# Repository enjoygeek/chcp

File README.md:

chcp
====

PoE powered, IPv6 Central Heating Control Panel

Photo of circuit board:

More photos in this gallery on Flickr:
https://www.flickr.com/photos/njh/sets/72157648035750106/

ATMEGA328 Pin Mapping
----------------------

| Pin | Port | Arduino | Function    |
|-----|------|---------|-------------|
| 1   | RST# |         |             |
| 2   | D0   | D0      | Serial RX   |
| 3   | D1   | D1      | Serial TX   |
| 4   | D2   | D2      |             |
| 5   | D3   | D3      | LCD LIGHT   |
| 6   | D4   | D4      |             |
| 7   | VCC  |         |             |
| 8   | GND  |         |             |
| 9   | CLK  |         |             |
| 10  | CLK  |         |             |
| 11  | D5   | D5      | Push Button |
| 12  | D6   | D6      | Red LED     |
| 13  | D7   | D7      | Ethernet SS |
| 14  | B0   | D8      | LCD RESET   |
| 15  | B1   | D9      | LCD SS      |
| 16  | B2   | D10     | LCD DC      |
| 17  | B3   | D11     | SPI MOSI    |
| 18  | B4   | D12     | SPI MISO    |
| 19  | B5   | D13     | SPI SCLK    |
| 20  | VCC  |         |             |
| 21  | Aref |         |             |
| 22  | GND  |         |             |
| 23  | C0   | A0      |             |
| 24  | C1   | A1      |             |
| 25  | C2   | A2      |             |
| 26  | C3   | A3      |             |
| 27  | C4   | A4      | I2C SDA     |
| 28  | C5   | A5      | I2C SCL     |

PoE Pin Mapping
---------------

| RJ45 | IN28J60 | PEM1300 |
|------|---------|---------|
| 1+2  | POE+1   | VA1     |
| 3+6  | POE-1   | VA2     |
| 4+5  | POE-2   | VB1     |
| 7+8  | POE+2   | VB2     |

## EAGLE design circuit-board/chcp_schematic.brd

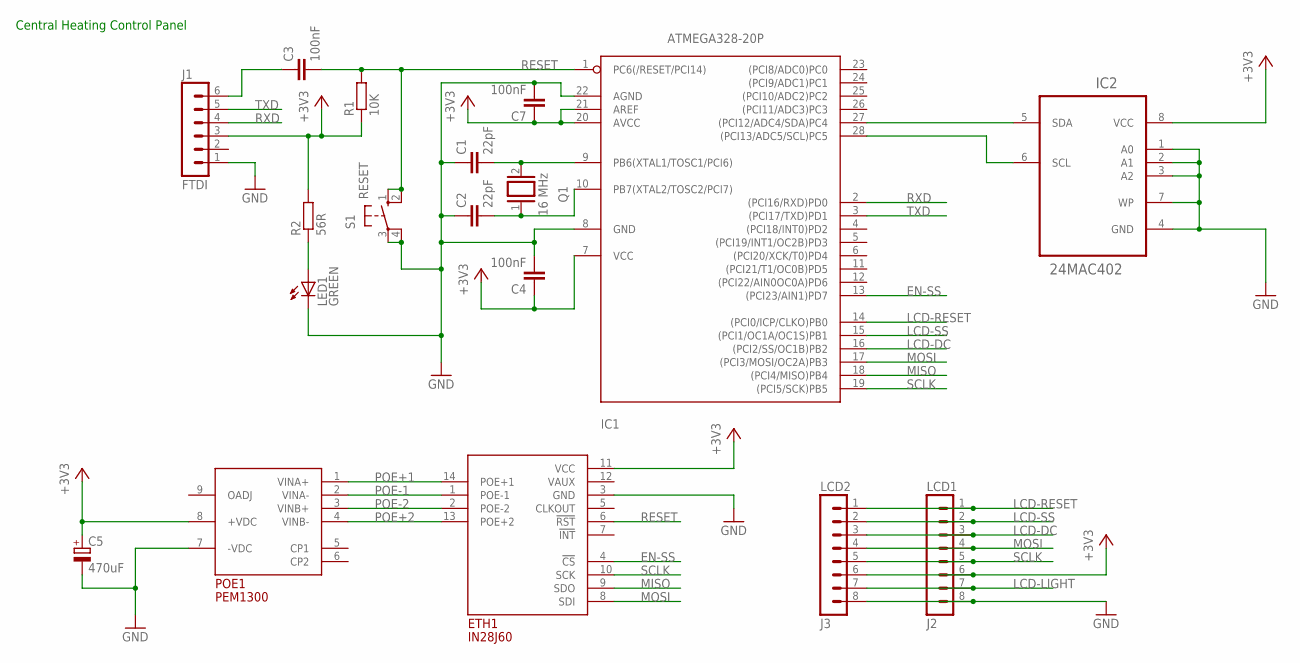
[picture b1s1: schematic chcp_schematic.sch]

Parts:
C1, C2: 22pF; C025-024X044
C3, C4, C7: 100nF; C025-024X044
C5: 470uF; E2,5-5
ETH1: IN28J60; DIL
IC1: ATMEGA328-20P; DIL28-3
IC2: 24MAC402; PDIP
J1: FTDI; MA06-1
J2: LCD1; MA08-1
J3: LCD2; MA08-1
LED1: GREEN; LED3MM
POE1: PEM1300; SIL
Q1: 16 MHz; QS
R1: 10K; 0204/7
R2: 56R; 0204/7
S1: RESET; B3F-10XX

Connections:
+3V3: C4.1, C5.+, C7.1, ETH1.11 (VCC), IC1.7 (VCC), IC1.20 (AVCC), IC1.21 (AREF), IC2.8 (VCC), J1.3, J2.6, J3.6, POE1.8 (+VDC), R1.1, R2.2
EN-SS: ETH1.4 (!CS!), IC1.13 ((PCI23/AIN1)PD7)
GND: C1.1, C2.1, C4.2, C5.-, C7.2, ETH1.3 (GND), IC1.8 (GND), IC1.22 (AGND), IC2.1 (A0), IC2.2 (A1), IC2.3 (A2), IC2.4 (GND), IC2.7 (WP), J1.1, J2.8, J3.8, LED1.K (C), POE1.7 (-VDC), S1.3, S1.4 (P1)
LCD-DC: IC1.16 ((PCI2/SS/OC1B)PB2), J2.3, J3.3
LCD-LIGHT: J2.7, J3.7
LCD-RESET: IC1.14 ((PCI0/ICP/CLKO)PB0), J2.1, J3.1
LCD-SS: IC1.15 ((PCI1/OC1A/OC1S)PB1), J2.2, J3.2
MISO: ETH1.9 (SDO), IC1.18 ((PCI4/MISO)PB4)
MOSI: ETH1.8 (SDI), IC1.17 ((PCI3/MOSI/OC2A)PB3), J2.4, J3.4
unnamed: C2.2, IC1.10 (PB7(XTAL2/TOSC2/PCI7)), Q1.1
unnamed: IC1.27 ((PCI12/ADC4/SDA)PC4), IC2.5 (SDA)
unnamed: IC1.28 ((PCI13/ADC5/SCL)PC5), IC2.6 (SCL)
unnamed: C3.1, J1.6
unnamed: C1.2, IC1.9 (PB6(XTAL1/TOSC1/PCI6)), Q1.2
unnamed: LED1.A, R2.1
POE+1: ETH1.14 (POE+1), POE1.1 (VINA+)
POE+2: ETH1.13 (POE+2), POE1.4 (VINB-)
POE-1: ETH1.1 (POE-1), POE1.2 (VINA-)
POE-2: ETH1.2 (POE-2), POE1.3 (VINB+)
RESET: C3.2, ETH1.6 (!RST!), IC1.1 (PC6(/RESET/PCI14)), R1.2, S1.1 (S), S1.2 (S1)
RXD: IC1.2 ((PCI16/RXD)PD0), J1.4
SCLK: ETH1.10 (SCK), IC1.19 ((PCI5/SCK)PB5), J2.5, J3.5
TXD: IC1.3 ((PCI17/TXD)PD1), J1.5

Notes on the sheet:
Central Heating Control Panel

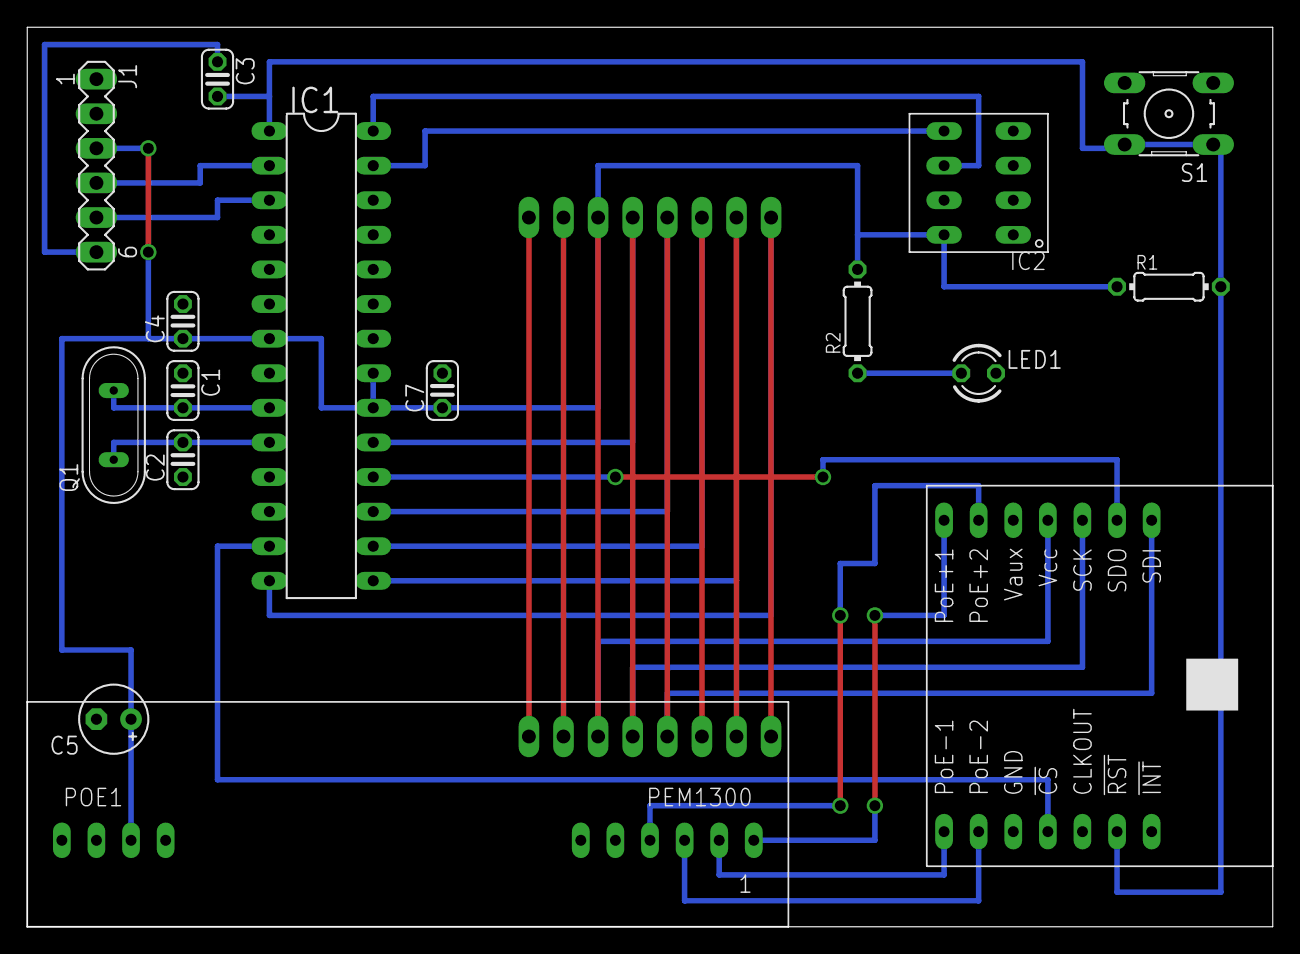
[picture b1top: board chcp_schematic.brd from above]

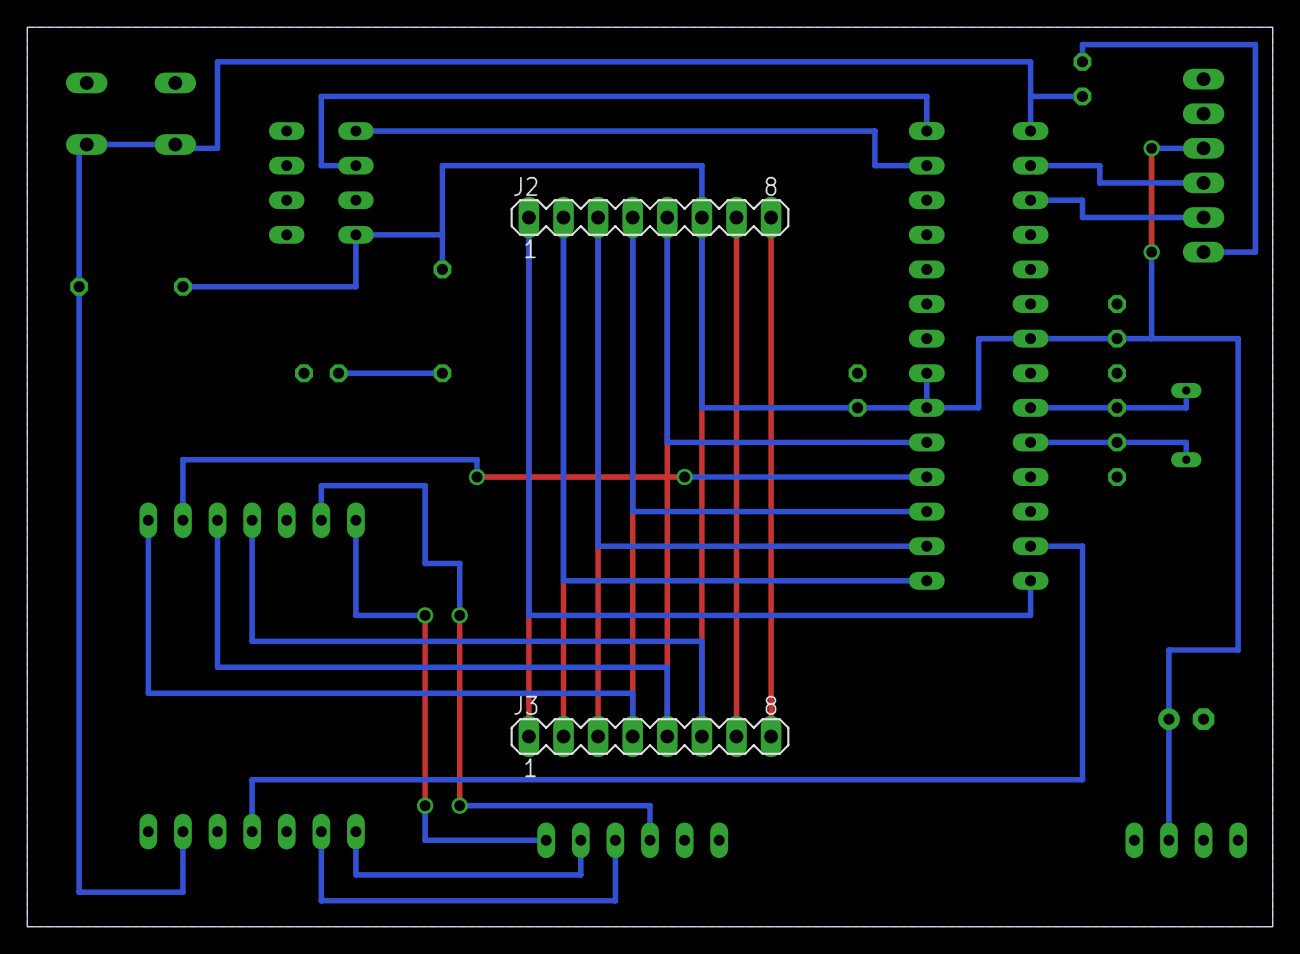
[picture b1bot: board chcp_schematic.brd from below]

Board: 2 copper layers, 91.4 x 66.0 mm, 18 parts (2 on the bottom side), 23 nets.

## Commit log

2014-03-09 Added gitignore for Eagle https://github.com/github/gitignore/blob/master/Eagle.gitignore
2014-03-09 Added work in progress of my Central Heating Control Panel schematic
2014-03-15 Created a block diagram of the circuit
2014-03-15 Created basic Arduino sketch
2014-03-15 Added block diagram to README.md
2014-03-15 Added PoE module model number to the block diagram
2014-03-16 Created 60x24 pixel bitmaps for the ON and OFF states
2014-03-16 Wrote perl script to convert PGM bitmap files to LCD byte arrays
2014-03-31 Implemented getting the server IP from DHCP and sending UDP messages to Node-RED
2014-04-21 Moved circuit board into sperate directory
2014-04-21 Made custom parts for the modules instead of using headers
2014-04-21 Removed the unnecessary capacitor connected to AREF
2014-04-21 Gave jumpers both names and values
2014-04-21 Finished laying out first version of the board
2014-04-21 Added 3mm Green Power LED
2014-09-26 Added PoE pin mapping to README
2014-09-26 Added ATMEGA328 pin mapping to README
2014-09-26 Renamed Ag900-S to PEM1300 in the block diagram
2014-09-27 Update README.md
    Added photo of board
2014-09-27 Update README.md
    Correct pin assignments
2014-09-27 Added Red LED and Push Button to the schematic
2014-09-27 Don't initialise serial - we aren't using it any more
2014-09-27 Updated PIN numbers to match the new PCB board
2014-09-27 Changed button to use internal pull up resistor and be active LOW
2014-09-27 Display MAC address on screen
2014-09-27 Display the ethernet chip version number
2017-04-01 Changed bitmap arrays to be const
2017-04-01 Converted to IPv6/EtherSia
2017-04-01 Added PDF of the schematic
2017-04-01 Updated README to mention IPv6
